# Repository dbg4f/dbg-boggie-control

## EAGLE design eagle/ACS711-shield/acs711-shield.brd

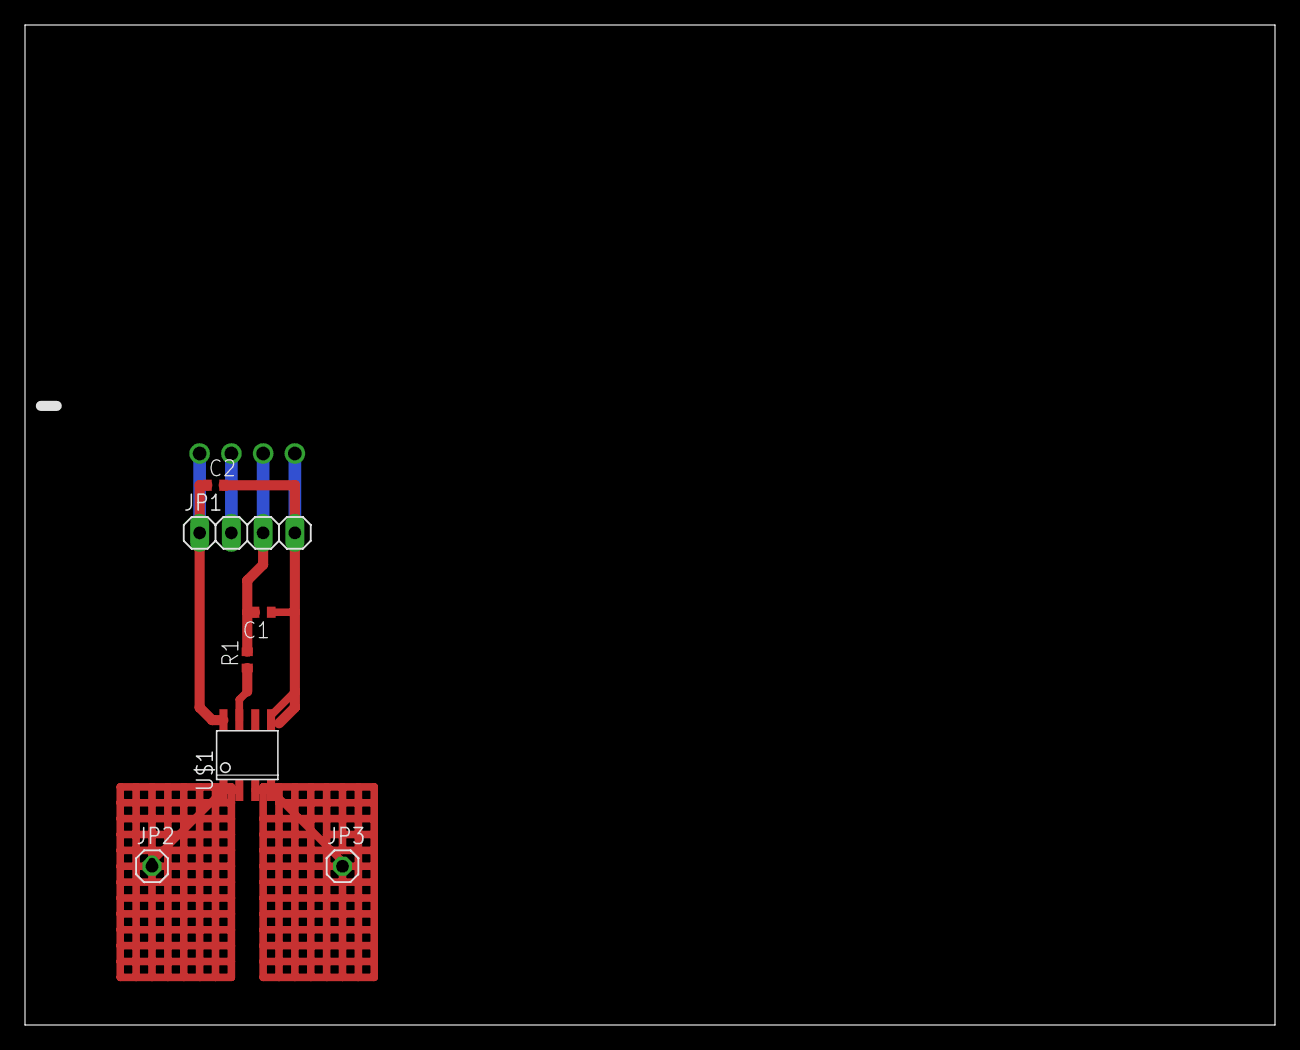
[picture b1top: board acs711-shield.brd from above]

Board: 2 copper layers, 100.0 x 80.0 mm, 7 parts (0 on the bottom side), 6 nets.

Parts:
C1, C2: 1; C0402
JP1: 1; 1X04
JP2, JP3: 1; 1X01
R1: 1; R0402
U$1: ACS711; SOIC8

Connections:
unnamed: JP2.1, U$1.1, U$1.2
unnamed: C1.1, C2.2, JP1.4, U$1.5
unnamed: C1.2, JP1.3, R1.2
unnamed: C2.1, JP1.1, U$1.8
unnamed: R1.1, U$1.7
unnamed: JP3.1, U$1.3, U$1.4

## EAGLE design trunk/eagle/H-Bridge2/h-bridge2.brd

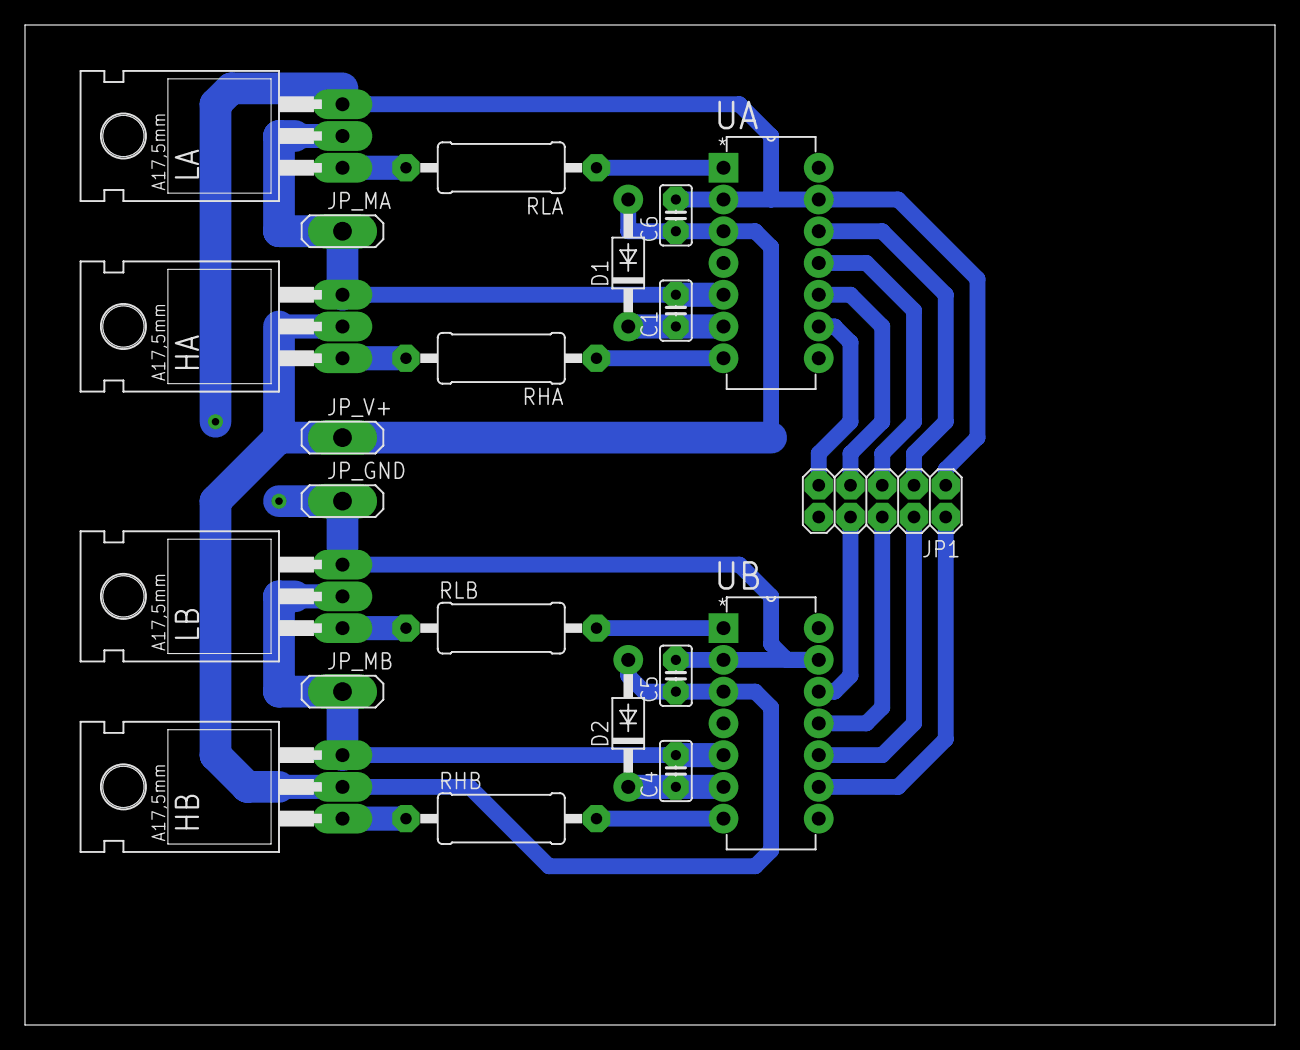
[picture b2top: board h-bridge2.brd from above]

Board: 2 copper layers, 100.0 x 80.0 mm, 21 parts (0 on the bottom side), 22 nets.

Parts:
C1, C4, C5, C6: C025-025X050
D1, D2: 1N4004; DO41-10
HA: IRLZ44Z; TO220BH
HB: IRLZ44Z; TO220BH
JP1: 2X05
JP_GND: 1X01
JP_MA: 1X01
JP_MB: 1X01
JP_V+: 1X01
LA: IRLZ44Z; TO220BH
LB: IRLZ44Z; TO220BH
RHA: 0411/15
RHB: 0411/15
RLA: 0411/15
RLB: 0411/15
UA: IR2110PBF; DIP254P762X533-14
UB: IR2110PBF; DIP254P762X533-14

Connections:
unnamed: C5.2, C6.2, JP1.1, JP_GND.1, LA.S, LB.S, UA.2, UA.13, UB.2, UB.13
unnamed: LA.G, RLA.2
unnamed: HA.G, RHA.2
unnamed: HB.G, RHB.1
unnamed: LB.G, RLB.1
unnamed: RHA.1, UA.7
unnamed: RLA.1, UA.1
unnamed: RHB.2, UB.7
unnamed: RLB.2, UB.1
unnamed: C5.1, C6.1, D1.A, D2.A, HA.D, HB.D, JP_V+.1, UA.3, UB.3
unnamed: C1.1, D1.C, UA.6
unnamed: C4.2, HB.S, JP_MB.1, LB.D, UB.5
unnamed: C1.2, HA.S, JP_MA.1, LA.D, UA.5
unnamed: C4.1, D2.C, UB.6
unnamed: JP1.5, UA.11
unnamed: JP1.9, UA.9
unnamed: JP1.7, UA.10
unnamed: JP1.3, UA.12
unnamed: JP1.2, UB.9
unnamed: JP1.4, UB.10
unnamed: JP1.6, UB.11
unnamed: JP1.8, UB.12

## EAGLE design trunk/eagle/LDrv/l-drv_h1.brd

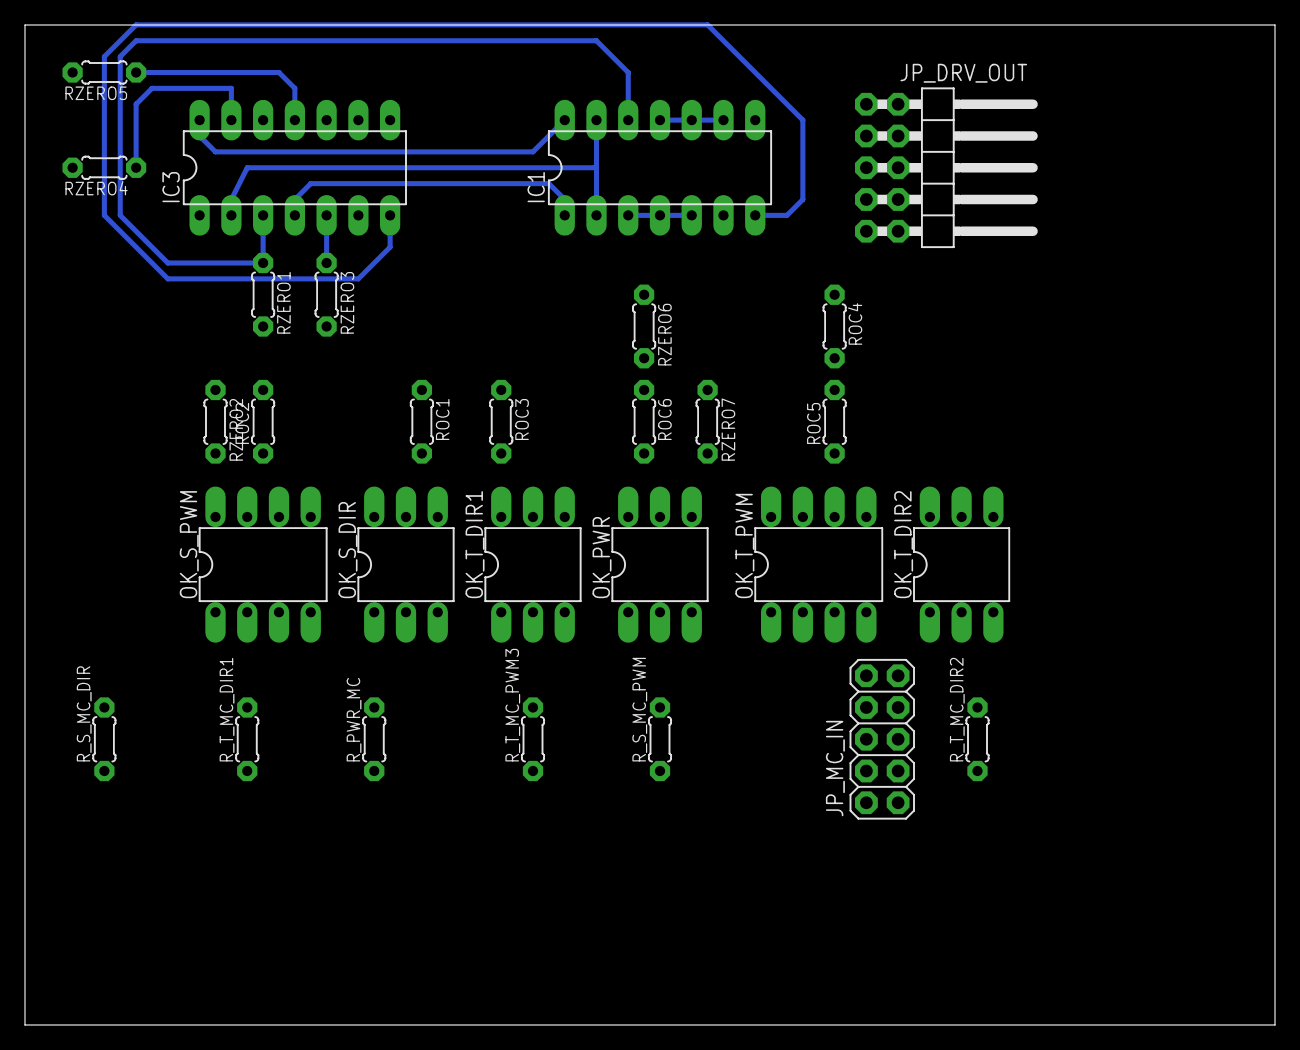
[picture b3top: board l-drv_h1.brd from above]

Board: 2 copper layers, 100.0 x 80.0 mm, 29 parts (0 on the bottom side), 38 nets.

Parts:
IC1: 74HC132N; DIL14
IC3: 74HC04N; DIL14
JP_DRV_OUT: 2X05/90
JP_MC_IN: 2X05
OK_PWR: 4N25M; DIL06
OK_S_DIR: 4N25M; DIL06
OK_S_PWM: 6N137; DIL08
OK_T_DIR1, OK_T_DIR2: 4N25M; DIL06
OK_T_PWM: 6N137; DIL08
ROC1, ROC2, ROC3, ROC4, ROC5, ROC6: 0204/5
RZERO1, RZERO2, RZERO3, RZERO4, RZERO5, RZERO6, RZERO7: 0204/5
R_PWR_MC: 0204/5
R_S_MC_DIR: 0204/5
R_S_MC_PWM: 0204/5
R_T_MC_DIR1, R_T_MC_DIR2: 0204/5
R_T_MC_PWM3: 0204/5

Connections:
GND: IC1.7, IC3.7, OK_PWR.4, OK_S_DIR.4, OK_S_PWM.5, OK_T_DIR1.4, OK_T_DIR2.4, OK_T_PWM.5, RZERO7.2
MC_GND: JP_MC_IN.9, OK_PWR.2, OK_S_DIR.2, OK_S_PWM.3, OK_T_DIR1.2, OK_T_DIR2.2, OK_T_PWM.3
unnamed: OK_S_DIR.1, R_S_MC_DIR.2
unnamed: OK_S_PWM.2, R_S_MC_PWM.2
unnamed: OK_T_DIR1.1, R_T_MC_DIR1.2
unnamed: OK_T_DIR2.1, R_T_MC_DIR2.2
unnamed: OK_T_PWM.2, R_T_MC_PWM3.2
unnamed: JP_MC_IN.2, R_S_MC_DIR.1
unnamed: JP_MC_IN.4, R_S_MC_PWM.1
unnamed: JP_MC_IN.5, R_T_MC_DIR1.1
unnamed: JP_MC_IN.3, R_T_MC_DIR2.1
unnamed: JP_MC_IN.1, R_T_MC_PWM3.1
unnamed: OK_T_DIR1.5, ROC3.1, RZERO3.2
unnamed: IC1.12, IC3.3, RZERO1.1
unnamed: OK_T_PWM.7, ROC5.1, RZERO5.2
unnamed: OK_PWR.1, R_PWR_MC.2
unnamed: OK_T_DIR2.5, ROC4.1, RZERO4.2
unnamed: JP_MC_IN.7, R_PWR_MC.1
unnamed: OK_S_PWM.7, ROC2.1, RZERO2.2
unnamed: OK_S_DIR.5, ROC1.1, RZERO1.2
unnamed: OK_PWR.5, ROC6.1, RZERO6.2
unnamed: IC3.8, JP_DRV_OUT.9
unnamed: IC3.10, JP_DRV_OUT.7
unnamed: IC3.12, JP_DRV_OUT.5
unnamed: IC3.6, JP_DRV_OUT.3
unnamed: IC1.6, JP_DRV_OUT.4
unnamed: IC1.8, JP_DRV_OUT.2
unnamed: IC1.2, IC1.13, IC3.2
unnamed: IC1.1, IC3.4
unnamed: IC1.3, IC1.4, IC1.5
unnamed: IC1.9, IC1.10, IC1.11
unnamed: IC3.1, RZERO2.1
unnamed: IC3.5, RZERO3.1
unnamed: IC3.13, RZERO4.1
unnamed: IC3.11, RZERO5.1
unnamed: IC3.9, RZERO6.1
unnamed: JP_DRV_OUT.8, JP_DRV_OUT.10, RZERO7.1
VCC: IC1.14, IC3.14, JP_DRV_OUT.1, OK_S_PWM.8, OK_T_PWM.8, ROC1.2, ROC2.2, ROC3.2, ROC4.2, ROC5.2, ROC6.2

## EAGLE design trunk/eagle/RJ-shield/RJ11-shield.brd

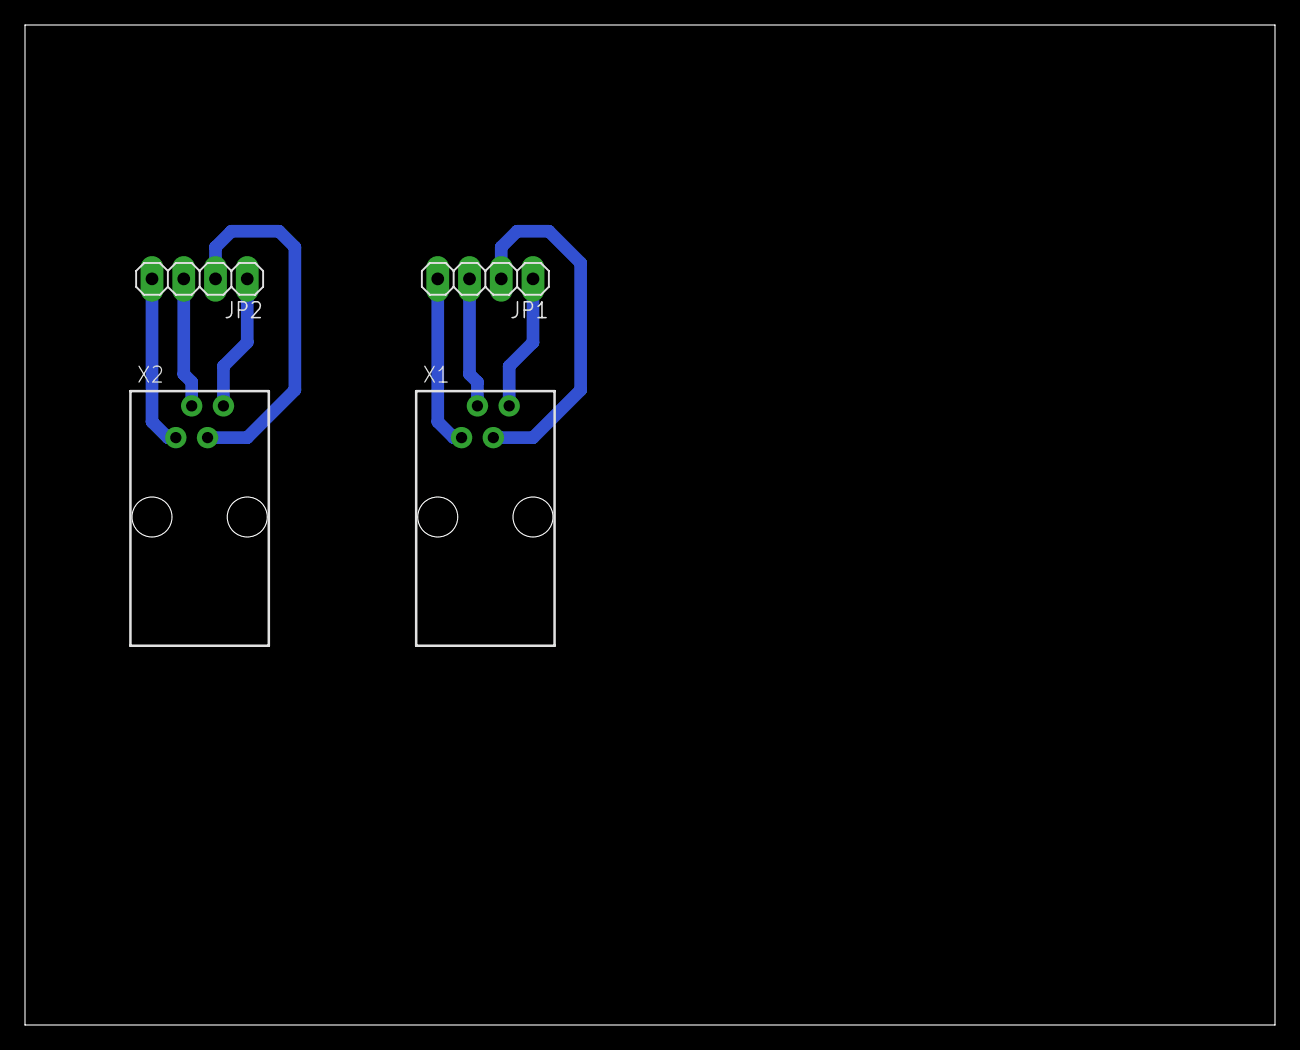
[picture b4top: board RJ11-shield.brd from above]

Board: 2 copper layers, 100.0 x 80.0 mm, 4 parts (0 on the bottom side), 8 nets.

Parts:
JP1, JP2: 1X04
X1, X2: 14867

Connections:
unnamed: JP1.4, X1.1
unnamed: JP1.3, X1.2
unnamed: JP1.2, X1.3
unnamed: JP1.1, X1.4
unnamed: JP2.4, X2.1
unnamed: JP2.3, X2.2
unnamed: JP2.2, X2.3
unnamed: JP2.1, X2.4
